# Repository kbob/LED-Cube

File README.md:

# LED Cube

A cube made of RGB LED panels.

I saw [Zaurak's and Polyfloyd's LED cubes](https://kbob.github.io/2019/08/23/led-cubes.html), and decided I wanted to make one too.  This one is smaller with denser LEDs.  (2mm pitch instead of 2.5mm)

# Overview

The cube's faces are six LED panels from Aliexpress.  Each panel has 64&times;64 RGB leds and is driven by the HUB75 protocol.

The chassis is a combination of 3D printed PLA, machine screws, and magnets.
The electronics can be installed and removed without tools.

The electronics consist of a Raspberry Pi connected via USB to an
[iCEBreaker FPGA](https://www.crowdsupply.com/1bitsquared/icebreaker-fpga)
dev board, HUB75 PMOD interface, and the panels.

Power is provided by an eight pack of 18650 batteries and a custom
power supply.  The power board also has an inertial measurement
unit (IMU), battery level monitoring, and soft power controls.

I also have two different display stands that prop the cube up on
one corner.  One stand disassembles for easy transport; the other, shown above,
is more stable and has a (bulky) carrying case.  All this is 3D printed.

# What's Here?

* **Mechanical/** CAD files, STL files, and parts lists.  The two
  display stands are here too.

* **Power Board/** KiCAD files and BOM for the custom power board.

* **Wiring/** Notes on the wiring harness.

* **Linux/** Notes on configuring Linux on the Raspberry Pi.

# What's Missing?

There are several different software options.  I outlined them in
[this 'blog post](https://kbob.github.io/2019-08-23/led-cubes.html).
None of them are in this repository.  I couldn't even begin
to write a comprehensive installation guide for them all.

The gateware is based on [tnt's excellent
ice40-playground](https://github.com/smunaut/ice40-playground).
But I have my own fork [here](https://github.com/kbob/ice40-playground).
My cube uses the `topic-cube` branch.  I haven't checked whether everything
in that branch has made it back upstream.

# What's Coming (I hope)?

## Raspberry Pi 4

My cube has a Raspberry Pi 3 Model A+.  (What a mouthful!)
Shortly after I built it, the Raspberry Pi foundation announced
the Raspberry Pi 4.  Its GPU is much better, and I really want to
get it into my cube.  But of course it's a different size;
I have to redesign part of the chassis to make it fit.

# Mesa OpenGL

I am using Broadcom's proprietary OpenGL.  I want to get the
open source Mesa GL running, but haven't figured out the magic
yet.  (It's complicated because I refuse to install an X11 server;
I only want offscreen rendering.)

# More LED Panels

**Update 2019-09-22:**  Good news!  1BitSquared now has [the correct
LED panels](https://1bitsquared.com/collections/embedded-hardware/products/led-panel)
in stock.  Get the ICN2037 variant.

The Aliexpress vendors do not ship a single version of the HUB75
panels.  Instead, you get whatever vendors happen to be available
surplus.  Each version has different driver chips, timing requirements,
mechanical layout, even power voltage requirements.  So today
the panels on the cube are irreplaceable.  If one dies, I'll
have no cube.

~~Esden is working on getting a reliable source for LED panels.
Follow him on twitter ([@esden](https://twitter.com/esden))
to stay up to date.~~

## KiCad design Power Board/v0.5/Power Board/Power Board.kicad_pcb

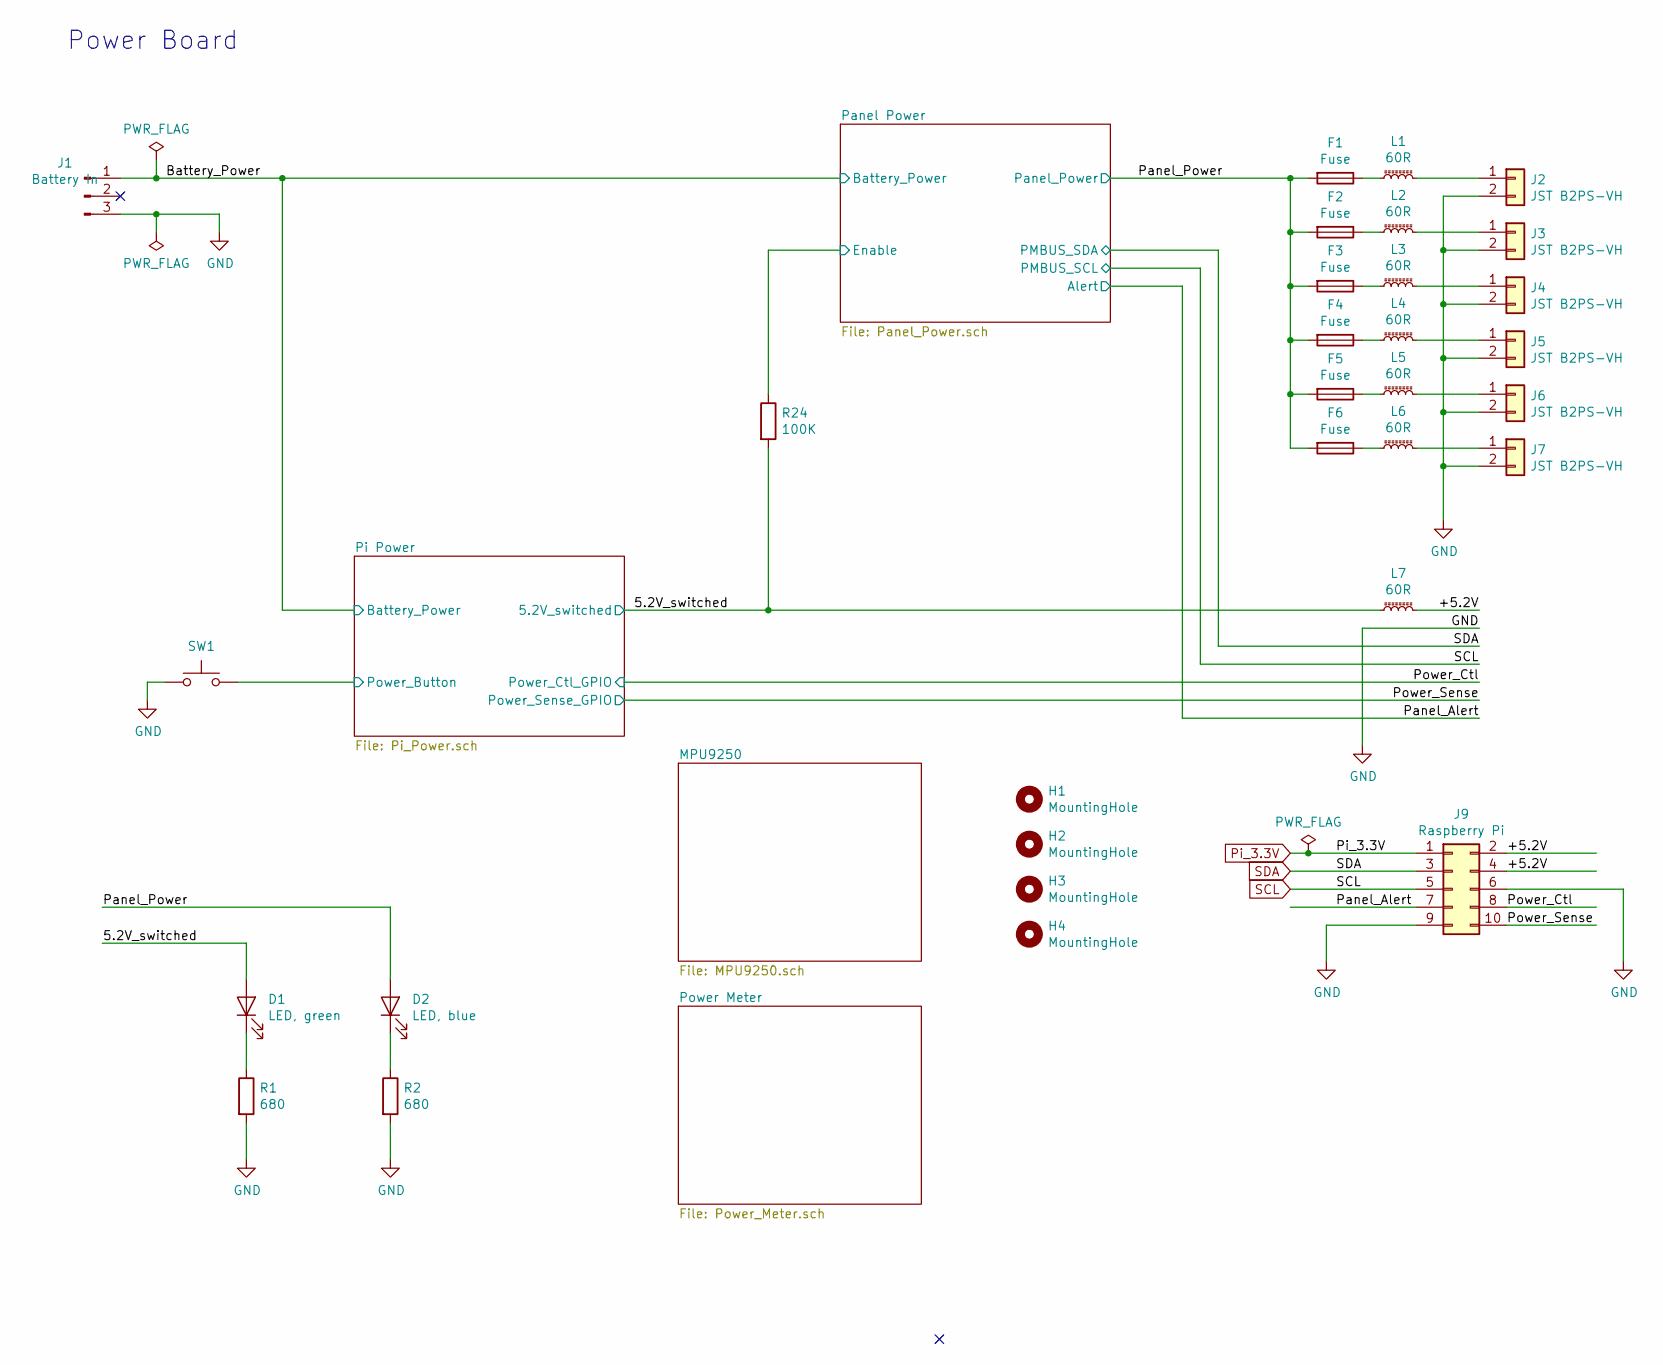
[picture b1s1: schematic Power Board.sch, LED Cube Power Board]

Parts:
D1: LED, green; LED_0603_1608Metric; Part No. LG Q971-KN-1
D2: LED, blue; LED_0603_1608Metric; Part No. LB Q39G-L2N2-35-1
F1, F2, F3, F4, F5, F6: Fuse; Fuse_1206_3216Metric; Part No. NANOSMD400LR-C-2; Digikey No. F9967CT-ND
H1, H2, H3, H4: MountingHole; MountingHole_2.7mm_M2.5
J1: Battery In; JST_VH_B3PS-VH_1x03_P3.96mm_Horizontal; Part No. B3PS-VH(LF)(SN); Digikey No. 455-1649-ND
J2, J3, J4, J5, J6, J7: JST B2PS-VH; JST_VH_B2PS-VH_1x02_P3.96mm_Horizontal; Part No. B2PS-VH(LF)(SN); Digikey No. 455-1648-ND
J9: Raspberry Pi; JST_PUD_S10B-PUDSS-1_2x05_P2.00mm_Horizontal; Part No. S10B-PUDSS-1(LF)(SN); Digikey No. 455-2486-ND
L1, L2, L3, L4, L5, L6, L7: 60R; L_1206_3216Metric; Part No. FBMJ3216HM600-T; Digikey No. 587-1770-1-ND
R1, R2: 680; R_0603_1608Metric_Pad1.05x0.95mm_HandSolder; Part No. RC0603JR-07680R
R24: 100K; R_0603_1608Metric; Part No. RC0603JR-07100K
SW1: SW_Push; PTS645-Vx-39-2; Part No. PTS645VK39-2 LFS; Digikey No. CKN10053-ND

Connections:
/5.2V_switched: D1.2 (A), L7.1, R24.2; also elsewhere on the board
/+5.2V: J9.2, J9.4, L7.2
/Battery_Power: J1.1; also elsewhere on the board
/Panel Power/Enable: R24.1; also elsewhere on the board
/Panel_Alert: J9.7; also elsewhere on the board
/Panel_Power: D2.2 (A), F1.2, F2.2, F3.2, F4.2, F5.2, F6.2; also elsewhere on the board
/Pi Power/Power_Button: SW1.2; also elsewhere on the board
/Power_Ctl: J9.8; also elsewhere on the board
/Power_Sense: J9.10; also elsewhere on the board
GND: J1.3, J2.2, J3.2, J4.2, J5.2, J6.2, J7.2, J9.6, J9.9, R1.2, R2.2, SW1.1; also elsewhere on the board
unnamed: D1.1 (K), R1.1
unnamed: D2.1 (K), R2.1
unnamed: F1.1, L1.1
unnamed: F2.1, L2.1
unnamed: F3.1, L3.1
unnamed: F4.1, L4.1
unnamed: F5.1, L5.1
unnamed: F6.1, L6.1
unnamed: J2.1, L1.2
unnamed: J3.1, L2.2
unnamed: J4.1, L3.2
unnamed: J5.1, L4.2
unnamed: J6.1, L5.2
unnamed: J7.1, L6.2
Pi_3.3V: J9.1; also elsewhere on the board
SCL: J9.5; also elsewhere on the board
SDA: J9.3; also elsewhere on the board

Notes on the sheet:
Power Board

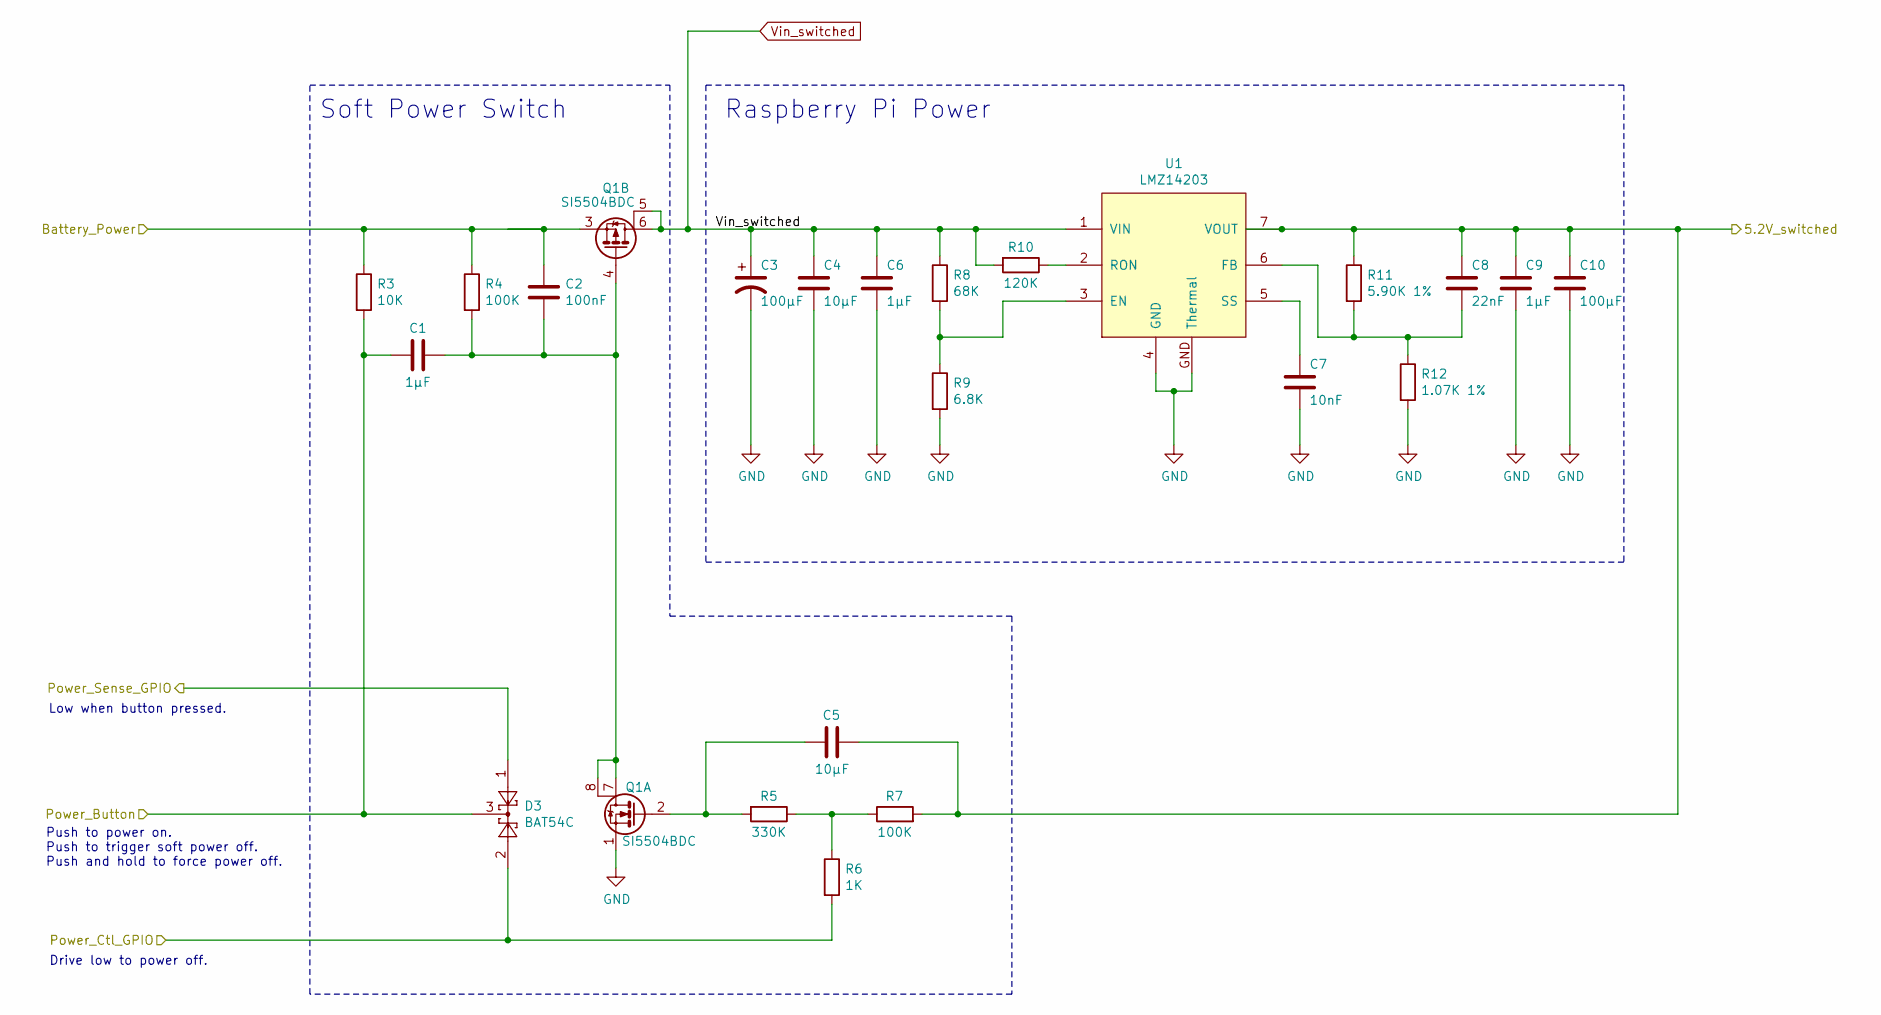
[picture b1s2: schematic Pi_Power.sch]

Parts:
C1, C6, C9: 1µF; C_0805_2012Metric; Part No. GMK212B7105KG-T; Digikey No. 587-1438-1-ND
C2: 100nF; C_0805_2012Metric; Part No. CGA4J2X7R2A104K125AA; Digikey No. 445-5827-1-ND
C3: 100µF; CP_Elec_8x10; Part No. EDK107M050A9MAA; Digikey No. 399-6672-1-ND
C4, C5: 10µF; C_0805_2012Metric; Part No. GRM21BR61E106MA73L; Digikey No. 490-10748-1-ND
C7: 10nF; C_0603_1608Metric; Part No. GRM188R71H103KA01D
C8: 22nF; C_0603_1608Metric; Part No. 885012206091; Digikey No. 732-8009-1-ND
C10: 100µF; C_1210_3225Metric; Part No. LMK325BJ107MM-T; Digikey No. 587-1965-1-ND
D3: BAT54C; SOT-23; Part No. BAT54CTA; Digikey No. BAT54CCT-ND
Q1: SI5504BDC; 1206-8_or_SO-8; Part No. SI5504BDC-T1-GE3; Digikey No. SI5504BDC-T1-GE3CT-ND
R3: 10K; R_0603_1608Metric; Part No. RC0603JR-0710K
R4, R7: 100K; R_0603_1608Metric; Part No. RC0603JR-07100K
R5: 330K; R_0603_1608Metric; Part No. RC0603JR-07330K
R6: 1K; R_0603_1608Metric; Part No. RC0603JR-071K
R8: 68K; R_0603_1608Metric; Part No. RC0603JR-0768K
R9: 6.8K; R_0603_1608Metric; Part No. RC0603JR-076K8
R10: 120K; R_0603_1608Metric; Part No. RC0603JR-07120K
R11: 5.90K 1%; R_0603_1608Metric; Part No. ERJ-3EKF5901V; Digikey No. P5.90KHCT-ND
R12: 1.07K 1%; R_0603_1608Metric; Part No. ERJ-3EKF1071V; Digikey No. P1.07KHCT-ND
U1: LMZ14203; TO-PMOD_7; Part No. LMZ14203TZX-ADJ/NOPB; Digikey No. LMZ14203TZX-ADJ/NOPBCT-ND

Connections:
/5.2V_switched: C5.2, C8.1, C9.1, C10.1, R7.2, R11.1, U1.7 (VOUT); also elsewhere on the board
/Battery_Power: C2.1, Q1.3 (1), R3.1, R4.1; also elsewhere on the board
/Pi Power/Power_Button: C1.2, D3.3, R3.2; also elsewhere on the board
/Power_Ctl: D3.2, R6.2; also elsewhere on the board
/Power_Sense: D3.1; also elsewhere on the board
GND: C3.2, C4.2, C6.2, C7.2, C9.2, C10.2, Q1.1 (S), R9.2, R12.2, U1.4 (GND), U1.GND (Thermal); also elsewhere on the board
unnamed: C1.1, C2.2, Q1.4 (G), Q1.7 (D), Q1.8 (D), R4.2
unnamed: C5.1, Q1.2 (G), R5.2
unnamed: C7.1, U1.5 (SS)
unnamed: C8.2, R11.2, R12.1, U1.6 (FB)
unnamed: R5.1, R6.1, R7.1
unnamed: R8.2, R9.1, U1.3 (EN)
unnamed: R10.1, U1.2 (RON)
Vin_switched: C3.1, C4.1, C6.1, Q1.5 (D), Q1.6 (D), R8.1, R10.2, U1.1 (VIN); also elsewhere on the board

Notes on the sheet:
Raspberry Pi Power
Push to power on. Push to trigger soft power off. Push and hold to force power off.
Drive low to power off.
Soft Power Switch
Low when button pressed.

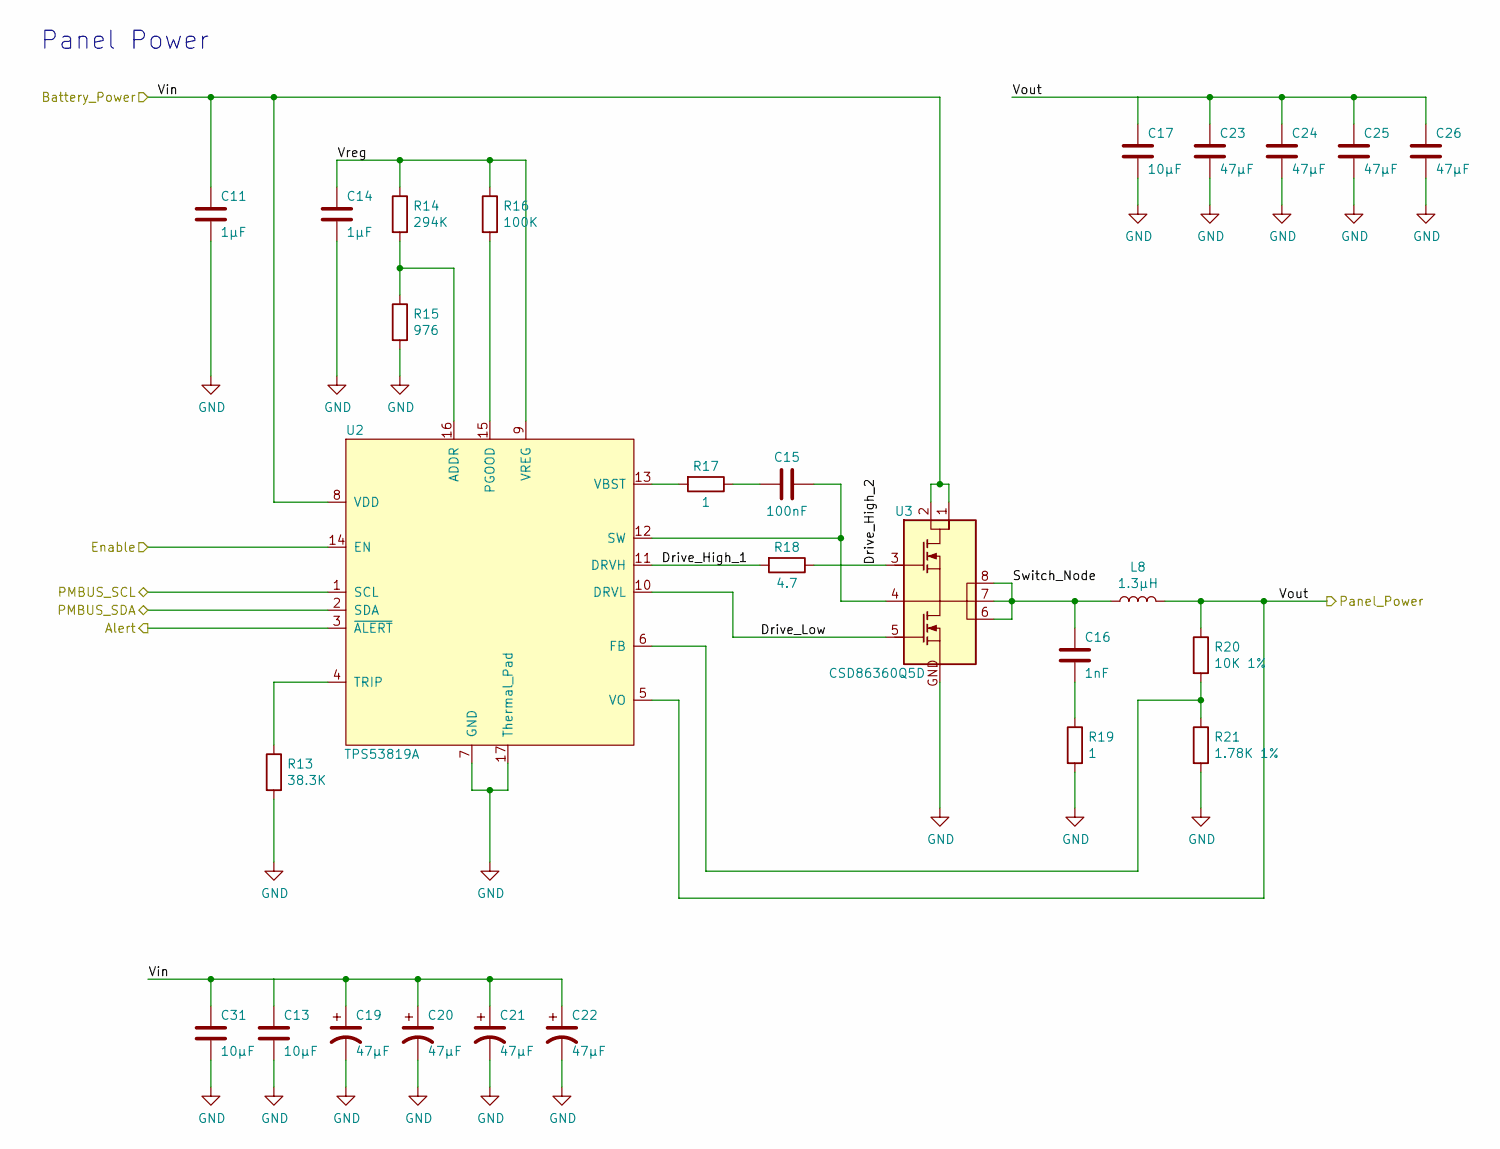
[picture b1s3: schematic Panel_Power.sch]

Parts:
C11, C14: 1µF; C_0805_2012Metric; Part No. GMK212B7105KG-T; Digikey No. 587-1438-1-ND
C13, C17, C31: 10µF; C_1206_3216Metric; Part No. GRM21BR61E106MA73L; Digikey No. 490-10748-1-ND
C15: 100nF; C_0805_2012Metric; Part No. CGA4J2X7R2A104K125AA; Digikey No. 445-5827-1-ND
C16: 1nF; C_0603_1608Metric; Part No. C0603C102J5RACTU; Digikey No. 399-1083-1-ND
C19, C20, C21, C22: 47µF; CP_OSCON_Poly_F12; Part No. 35SVPD47M; Digikey No. PCE5080CT-ND
C23, C24, C25, C26: 47µF; C_1210_3225Metric; Part No. GRM32EC81C476KE15L; Digikey No. 490-10531-1-ND
L8: 1.3µH; Coilcraft_XAL1580; Part No. XAL1580-132MEB; Digikey No. Mouser
R13: 38.3K; R_0603_1608Metric; Part No. RMCF0603FT38K3; Digikey No. RMCF0603FT38K3CT-ND
R14: 294K; R_0402_1005Metric; Part No. CRCW0402294KFKED; Digikey No. 541-294KLCT-ND
R15: 976; R_0402_1005Metric; Part No. CRCW0402976RFKED; Digikey No. 541-976LCT-ND
R16: 100K; R_0603_1608Metric; Part No. RC0603JR-07100K
R17, R19: 1; R_0805_2012Metric; Part No. CRCW08051R00FKEA; Digikey No. 541-1.00CCCT-ND
R18: 4.7; R_0805_2012Metric; Part No. ERJ-6RQF4R7V; Digikey No. P4.7DCT-ND
R20: 10K 1%; R_0603_1608Metric; Part No. RNCP0603FTD10K0; Digikey No. RNCP0603FTD10K0CT-ND
R21: 1.78K 1%; R_0603_1608Metric; Part No. RC0603FR-0717K8L; Digikey No. 311-17.8KHRCT-ND
U2: TPS53819A; VQFN-16-1EP_3x3mm_P0.5mm_EP1.68x1.68mm_ThermalVias; Part No. TPS53819ARGTR; Digikey No. 296-35480-1-ND
U3: CSD86360Q5D; Q5D; Part No. CSD86360Q5D; Digikey No. 296-35026-1-ND

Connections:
/Battery_Power: C11.1, C13.1, C19.1, C20.1, C21.1, C22.1, C31.1, U2.8 (VDD), U3.1 (VIN), U3.2 (VIN); also elsewhere on the board
/Panel Power/Drive_High_1: R18.2, U2.11 (DRVH)
/Panel Power/Drive_High_2: R18.1, U3.3 (TG)
/Panel Power/Drive_Low: U2.10 (DRVL), U3.5 (BG)
/Panel Power/Enable: U2.14 (EN); also elsewhere on the board
/Panel Power/Switch_Node: C16.1, L8.1, U3.6 (VSW), U3.7 (VSW), U3.8 (VSW)
/Panel Power/Vreg: C14.1, R14.1, R16.1, U2.9 (VREG)
/Panel_Alert: U2.3 (~ALERT); also elsewhere on the board
/Panel_Power: C17.1, C23.1, C24.1, C25.1, C26.1, L8.2, R20.1, U2.5 (VO); also elsewhere on the board
GND: C11.2, C13.2, C14.2, C17.2, C19.2, C20.2, C21.2, C22.2, C23.2, C24.2, C25.2, C26.2, C31.2, R13.2, R15.2, R19.2, R21.2, U2.7 (GND), U2.17 (Thermal_Pad), U3.GND; also elsewhere on the board
unnamed: C15.1, U2.12 (SW), U3.4 (TGR)
unnamed: C15.2, R17.1
unnamed: C16.2, R19.1
unnamed: R13.1, U2.4 (TRIP)
unnamed: R14.2, R15.1, U2.16 (ADDR)
unnamed: R16.2, U2.15 (PGOOD)
unnamed: R17.2, U2.13 (VBST)
unnamed: R20.2, R21.1, U2.6 (FB)
SCL: U2.1 (SCL); also elsewhere on the board
SDA: U2.2 (SDA); also elsewhere on the board

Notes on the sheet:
Panel Power

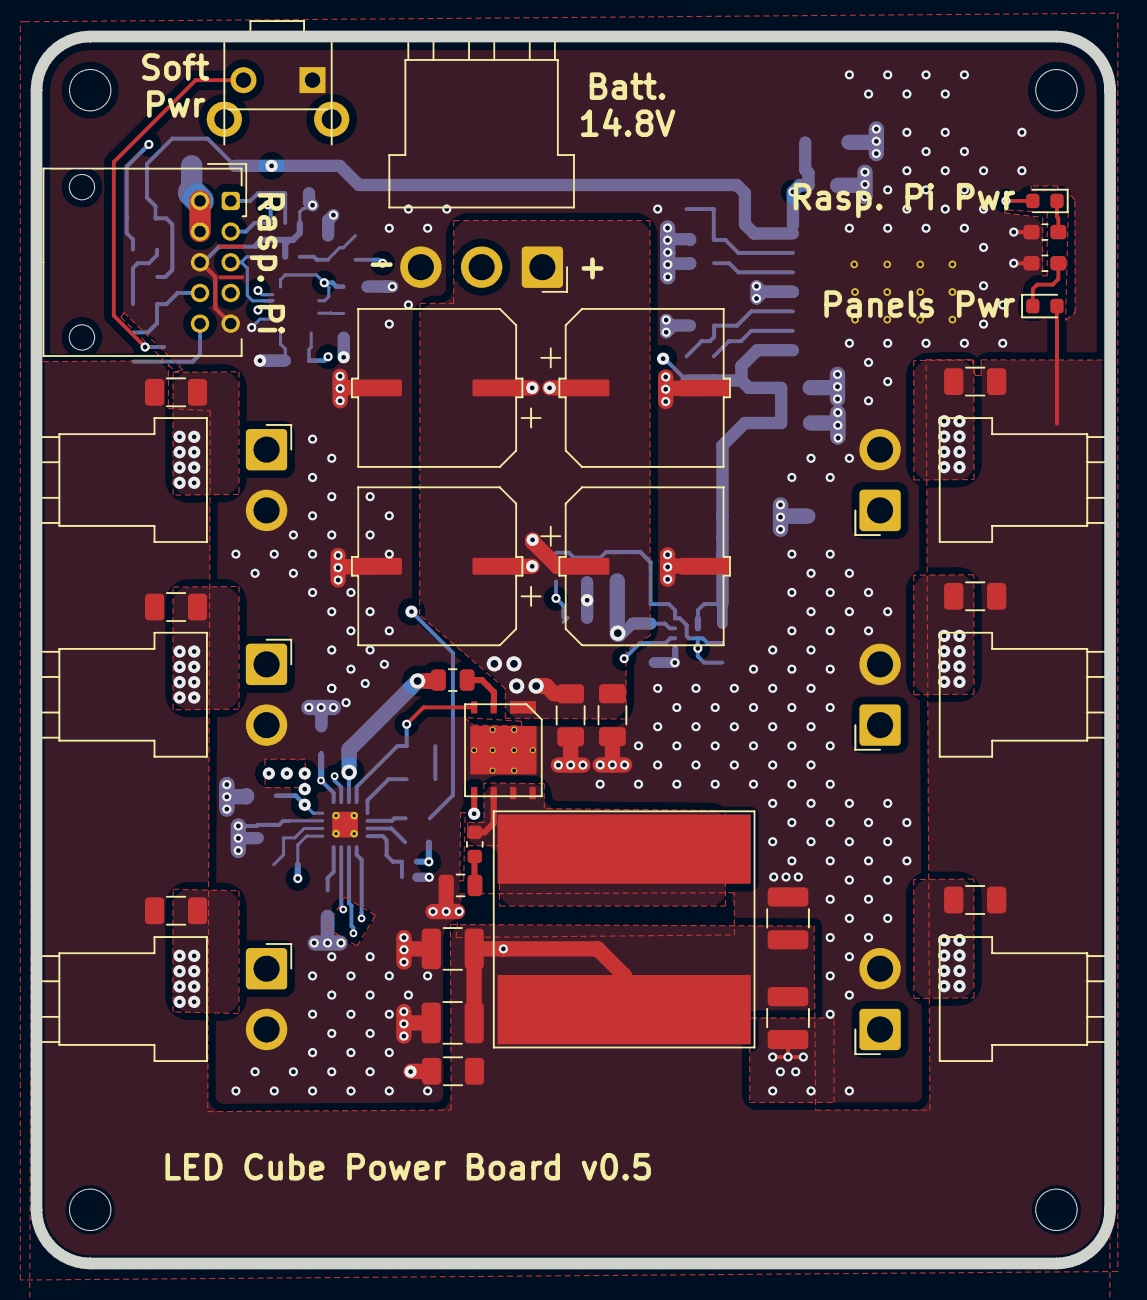
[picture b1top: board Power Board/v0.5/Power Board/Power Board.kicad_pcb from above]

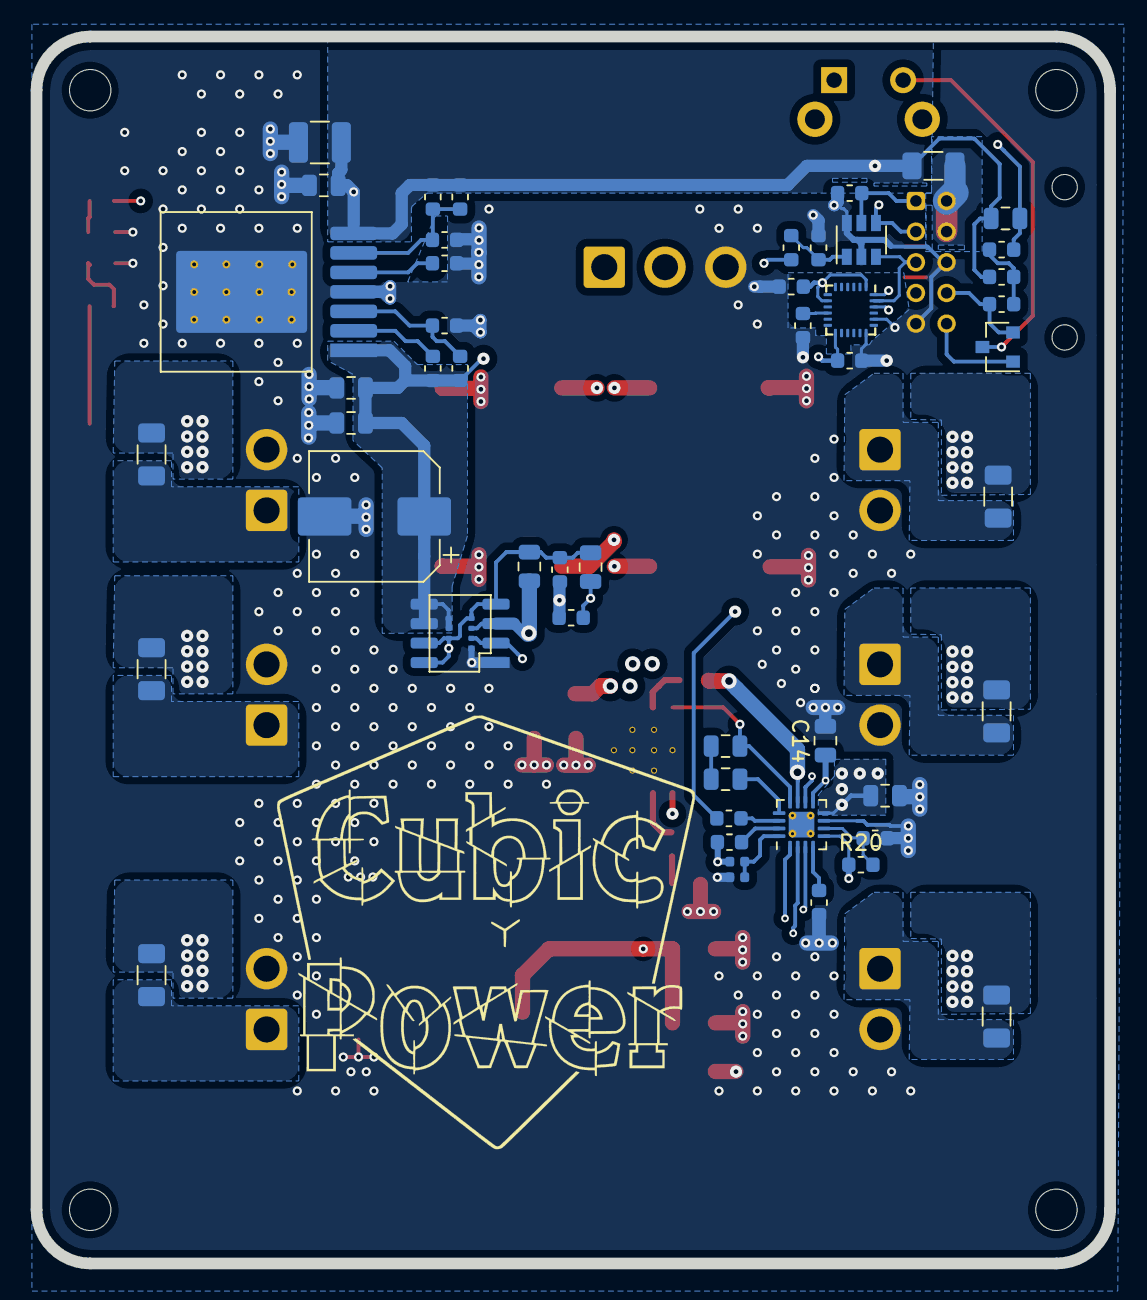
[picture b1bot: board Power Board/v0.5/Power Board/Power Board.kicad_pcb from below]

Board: 4 copper layers, 70.0 x 80.0 mm, 89 parts (50 on the bottom side), 50 nets.

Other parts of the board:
C27, C28, C30: 100nF; C_0603_1608Metric
C29: 10nF; C_0603_1608Metric
R22: 10K 1%; R_0603_1608Metric
R23: 1.78K 1%; R_0603_1608Metric
U4: MPU-9250; InvenSense_QFN-24_3x3mm_P0.4mm
U5: ADS1000; SOT-23-6

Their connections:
GND: C27.2, C28.2, C29.2, C30.2, R23.2, U4.18, U4.20, U5.2, U5.6; also elsewhere on the board
unnamed: C28.1, U4.10
unnamed: R22.2, R23.1, U5.1
Pi_3.3V: C27.1, C29.1, C30.1, U4.1, U4.8, U4.13, U4.22, U5.5; also elsewhere on the board
SCL: U4.23, U5.3; also elsewhere on the board
SDA: U4.24, U5.4; also elsewhere on the board
Vin_switched: R22.1; also elsewhere on the board

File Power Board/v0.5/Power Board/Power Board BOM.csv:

Reference, Quantity, Value, Footprint, Datasheet, Digikey No., Manufacturer, Part No., Package
C10 ,1,"100µF","Capacitor_SMD:C_1210_3225Metric","~","587-1965-1-ND","Taiyo Yuden","LMK325BJ107MM-T",""
C16 ,1,"1nF","Capacitor_SMD:C_0603_1608Metric","~","399-1083-1-ND","Kemet","C0603C102J5RACTU",""
C17 C13 C31 ,3,"10µF","Capacitor_SMD:C_1206_3216Metric","~","490-10748-1-ND","Murata","GRM21BR61E106MA73L",""
C19 C20 C21 C22 ,4,"47µF","Power_Board:CP_OSCON_Poly_F12","~","PCE5080CT-ND","Panasonic","35SVPD47M",""
C2 C15 ,2,"100nF","Capacitor_SMD:C_0805_2012Metric","~","445-5827-1-ND","TDK","CGA4J2X7R2A104K125AA",""
C23 C24 C25 C26 ,4,"47µF","Capacitor_SMD:C_1210_3225Metric","~","490-10531-1-ND","Murata","GRM32EC81C476KE15L",""
C28 C27 C30 ,3,"100nF","Capacitor_SMD:C_0603_1608Metric","~","-","Murata","GRM188R71C104KA01D",""
C3 ,1,"100µF","Capacitor_SMD:CP_Elec_8x10","https://datasheet.octopart.com/EDK107M050A9MAA-Kemet-datashe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","399-6672-1-ND","Kemet","EDK107M050A9MAA",""
C5 C4 ,2,"10µF","Capacitor_SMD:C_0805_2012Metric","~","490-10748-1-ND","Murata","GRM21BR61E106MA73L",""
C6 C9 C1 C14 C11 ,5,"1µF","Capacitor_SMD:C_0805_2012Metric","~","587-1438-1-ND","Taiyo Yuden","GMK212B7105KG-T",""
C7 C29 ,2,"10nF","Capacitor_SMD:C_0603_1608Metric","~","-","Murata","GRM188R71H103KA01D","0603"
C8 ,1,"22nF","Capacitor_SMD:C_0603_1608Metric","~","732-8009-1-ND","Wurth","885012206091",""
D1 ,1,"LED, green","LED_SMD:LED_0603_1608Metric","~","-","Osram","LG Q971-KN-1",""
D2 ,1,"LED, blue","LED_SMD:LED_0603_1608Metric","~","-","Osram","LB Q39G-L2N2-35-1",""
D3 ,1,"BAT54C","Package_TO_SOT_SMD:SOT-23","https://www.diodes.com/_files/datasheets/ds11005.pdf","BAT54CCT-ND","Diodes Inc.","BAT54CTA",""
F6 F5 F4 F3 F2 F1 ,6,"Fuse","Power_Board:Fuse_1206_3216Metric","~","F9967CT-ND","Littelfuse","NANOSMD400LR-C-2",""
H1 H2 H3 H4 ,4,"MountingHole","MountingHole:MountingHole_2.7mm_M2.5","~","-","-","-",""
J1 ,1,"Battery In","Power_Board:JST_VH_B3PS-VH_1x03_P3.96mm_Horizontal","","455-1649-ND","JST","B3PS-VH(LF)(SN)",""
J7 J6 J5 J4 J3 J2 ,6,"JST B2PS-VH","Power_Board:JST_VH_B2PS-VH_1x02_P3.96mm_Horizontal","~","455-1648-ND","JST","B2PS-VH(LF)(SN)",""
J9 ,1,"Raspberry Pi","Connector_JST:JST_PUD_S10B-PUDSS-1_2x05_P2.00mm_Horizontal","~","455-2486-ND","JST","S10B-PUDSS-1(LF)(SN)",""
L1 L2 L3 L4 L5 L6 L7 ,7,"60R","Inductor_SMD:L_1206_3216Metric","https://ds.yuden.co.jp/TYCOMPAS/ut/detail?pn=FBMJ3216HM600-T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","587-1770-1-ND","Taiyo Yuden","FBMJ3216HM600-T",""
L8 ,1,"1.3µH","Power_Board:Coilcraft_XAL1580","~","Mouser","Coilcraft","XAL1580-132MEB",""
Q1 ,1,"SI5504BDC","Power_Board:1206-8_or_SO-8","http://www.vishay.com/docs/74483/si5504bdc.pdf","SI5504BDC-T1-GE3CT-ND","Vishay","SI5504BDC-T1-GE3",""
R10 ,1,"120K","Resistor_SMD:R_0603_1608Metric","~","-","Yageo","RC0603JR-07120K","0603"
R11 ,1,"5.90K 1%","Resistor_SMD:R_0603_1608Metric","~","P5.90KHCT-ND","Panasonic","ERJ-3EKF5901V","0603"
R12 ,1,"1.07K 1%","Resistor_SMD:R_0603_1608Metric","~","P1.07KHCT-ND","Panasonic","ERJ-3EKF1071V","0603"
R13 ,1,"38.3K","Resistor_SMD:R_0603_1608Metric","~","RMCF0603FT38K3CT-ND","Stackpole","RMCF0603FT38K3",""
R14 ,1,"294K","Resistor_SMD:R_0402_1005Metric","~","541-294KLCT-ND","Vishay-Dale","CRCW0402294KFKED",""
R15 ,1,"976","Resistor_SMD:R_0402_1005Metric","~","541-976LCT-ND","VIshay-Dale","CRCW0402976RFKED",""
R17 R19 ,2,"1","Resistor_SMD:R_0805_2012Metric","~","541-1.00CCCT-ND","Vishay-Dale","CRCW08051R00FKEA",""
R18 ,1,"4.7","Resistor_SMD:R_0805_2012Metric","~","P4.7DCT-ND","Panasonic","ERJ-6RQF4R7V",""
R2 R1 ,2,"680","Resistor_SMD:R_0603_1608Metric_Pad1.05x0.95mm_HandSolder","~","-","Yageo","RC0603JR-07680R",""
R20 R22 ,2,"10K 1%","Resistor_SMD:R_0603_1608Metric","~","RNCP0603FTD10K0CT-ND","Stackpole","RNCP0603FTD10K0",""
R21 R23 ,2,"1.78K 1%","Resistor_SMD:R_0603_1608Metric","~","311-17.8KHRCT-ND","Yageo","RC0603FR-0717K8L",""
R24 R7 R4 R16 ,4,"100K","Resistor_SMD:R_0603_1608Metric","~","-","Yageo","RC0603JR-07100K",""
R3 ,1,"10K","Resistor_SMD:R_0603_1608Metric","~","-","Yageo","RC0603JR-0710K",""
R5 ,1,"330K","Resistor_SMD:R_0603_1608Metric","~","-","Yageo","RC0603JR-07330K",""
R6 ,1,"1K","Resistor_SMD:R_0603_1608Metric","~","-","Yageo","RC0603JR-071K",""
R8 ,1,"68K","Resistor_SMD:R_0603_1608Metric","~","-","Yageo","RC0603JR-0768K","0603"
R9 ,1,"6.8K","Resistor_SMD:R_0603_1608Metric","~","-","Yageo","RC0603JR-076K8","0603"
SW1 ,1,"SW_Push","Power_Board:PTS645-Vx-39-2","~","CKN10053-ND","C&K","PTS645VK39-2 LFS",""
U1 ,1,"LMZ14203","Power_Board:TO-PMOD_7","","LMZ14203TZX-ADJ/NOPBCT-ND","TI"," LMZ14203TZX-ADJ/NOPB ","TO-PMOD 7"
U2 ,1,"TPS53819A","Power_Board:VQFN-16-1EP_3x3mm_P0.5mm_EP1.68x1.68mm_ThermalVias","","296-35480-1-ND","TI","TPS53819ARGTR",""
U3 ,1,"CSD86360Q5D","Power_Board:Q5D","","296-35026-1-ND","TI","CSD86360Q5D",""
U4 ,1,"MPU-9250","Sensor_Motion:InvenSense_QFN-24_3x3mm_P0.4mm","https://store.invensense.com/datasheets/invensense/MPU9250RE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","1428-1019-1-ND","InvenSense","MPU-9250",""
U5 ,1,"ADS1000","Package_TO_SOT_SMD:SOT-23-6","http://www.ti.com/lit/ds/symlink/ads1000.pdf","296-38847-1-ND","TI","ADS1000A0IDBVR",""

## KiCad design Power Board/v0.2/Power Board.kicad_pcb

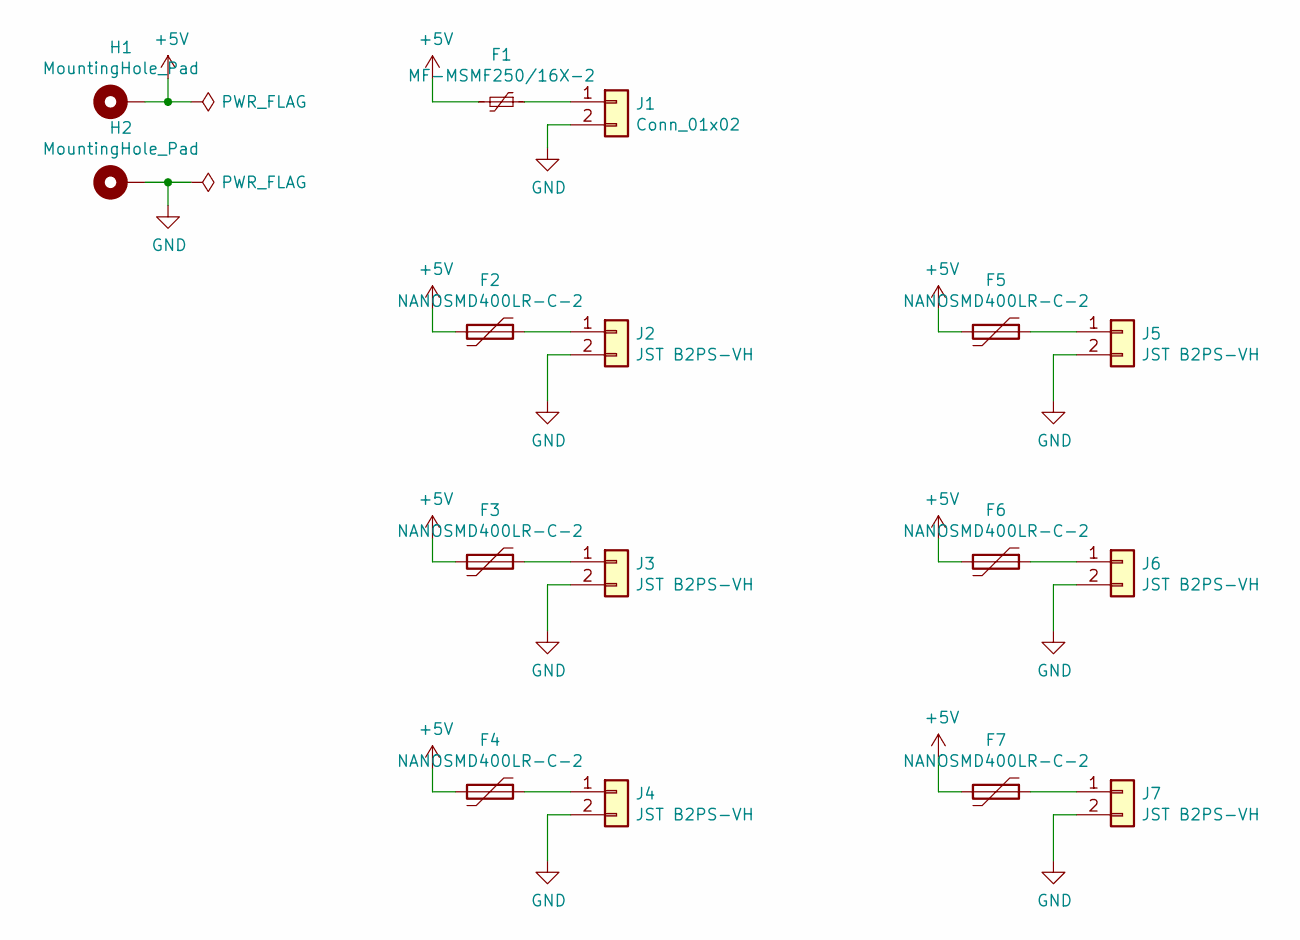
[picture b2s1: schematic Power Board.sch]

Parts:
F1: MF-MSMF250/16X-2; Bourns MF-MSMF Style 2
F2, F3, F4, F5, F6, F7: NANOSMD400LR-C-2; Fuse_1206_3216Metric
H1, H2: MountingHole_Pad; MountingHole_3mm_Pad
J1: Conn_01x02; PinSocket_1x02_P2.54mm_Horizontal
J2, J3, J4, J5, J6, J7: JST B2PS-VH; JST_VH_B2PS-VH_1x02_P3.96mm_Horizontal

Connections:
+5V: F1.2, F2.2, F3.2, F4.2, F5.2, F6.2, F7.2, H1.1
GND: H2.1, J1.2, J2.2, J3.2, J4.2, J5.2, J6.2, J7.2
unnamed: F1.1, J1.1
unnamed: F2.1, J2.1
unnamed: F3.1, J3.1
unnamed: F4.1, J4.1
unnamed: F5.1, J5.1
unnamed: F6.1, J6.1
unnamed: F7.1, J7.1

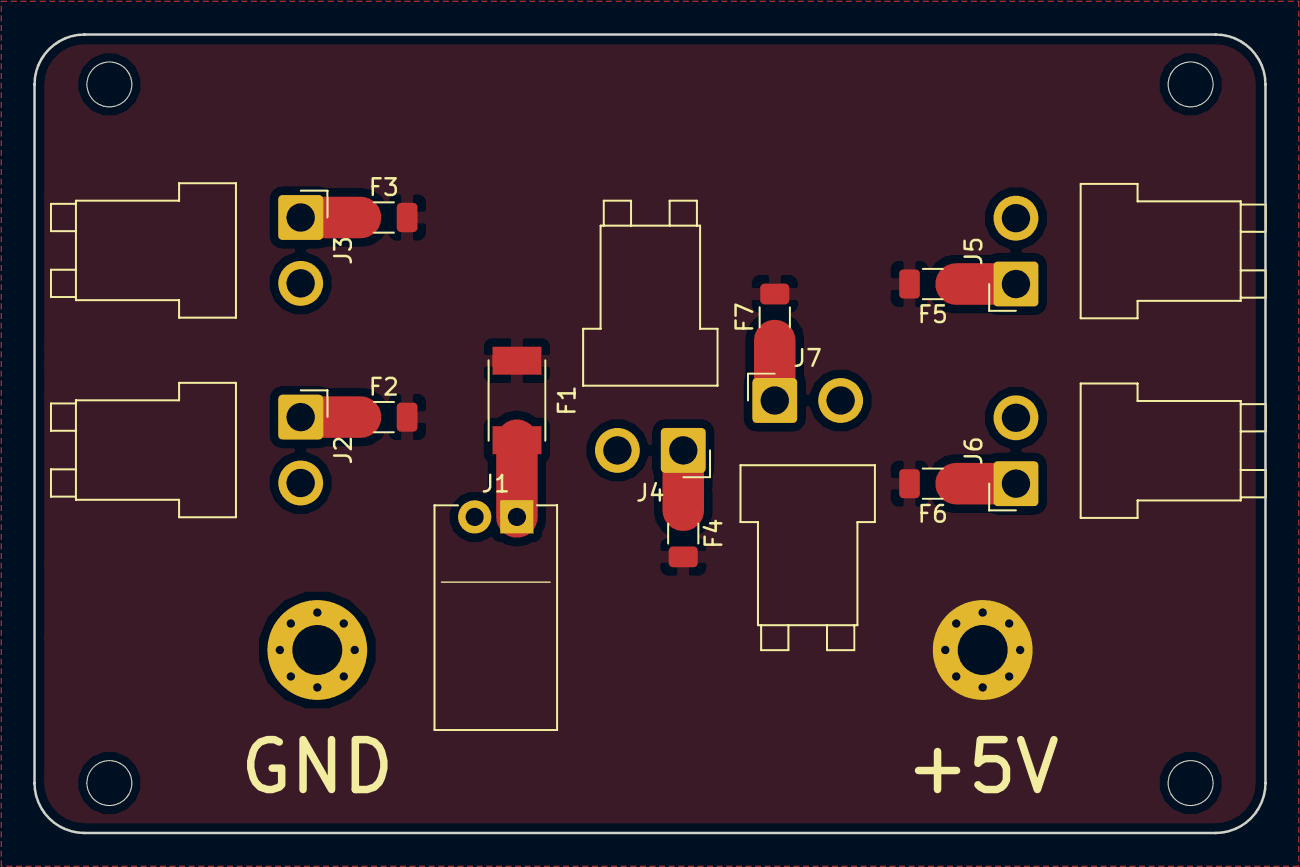
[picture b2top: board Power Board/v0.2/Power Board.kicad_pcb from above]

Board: 2 copper layers, 74.0 x 48.0 mm, 16 parts (0 on the bottom side), 9 nets.

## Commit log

2019-02-17 Power distribution board v0.1
2019-03-17 power board v0.2. Smaller fuses, smaller board.
2019-03-17 Add a README.
2019-03-20 Work in progress on v0.3 of power board.
2019-03-22 power board v0.3 - Raspberry Pi side only
2019-03-26 Oops, a no-connect was misaligned.
2019-03-26 Revised soft power switch. Now switches power to 5V regulator.
2019-03-27 Add datasheets.
2019-03-27 Remove Pi_Power.sch
2019-03-27 Rename Soft_Switch.sch to Pi_Power.sch
2019-03-28 Create the LED panel supply circuit.
2019-04-02 Update components with available parts.
2019-04-02 Document Raspberry Pi P1 connector wiring.
2019-04-03 Draw all custom footprints and assign to components.
2019-04-04 Work in progress.
2019-04-06 L8 footprint is Coilcraft XAL1580, not some Kemet cap.
2019-04-07 Start Power Board v0.4 by copying v0.3.
2019-04-07 Update schematic with panel power Cin, Cout.
2019-04-07 Update panel power with Cin, Cout.
2019-04-09 Add or correct courtyards.
2019-04-09 New 4 Layer Layout
    Needed 4 layers and double sided design in order to make everything fit
2019-04-11 Preliminary Layout Started
    Have most of the components moved to reasonable locations.
    Initial layout placeholders to get a general sense of connections.
    Added a sheet with the MPU-9250 Circuit but not pushed to board yet.
    Still need to add a lot of copper pours and stitching.
2019-04-12 More Layout Work
    Just another preliminary update so we can both work on changes
2019-04-14 Updated board dimensions and mt. holes, tweaked MPU schematic.
2019-04-14 Change keep-out text.
2019-04-15 Widen board to 70mm, delineate mechanical keepout zones.
2019-04-15 Revert "Change keep-out text."
    This reverts commit ca402f97387596ad30b5b3e9a838d0bd200cb8e0.
2019-04-15 Revert "Updated board dimensions and mt. holes, tweaked MPU schematic."
    This reverts commit 6936a160ef8a0f8efd2e8f2d18775030a6ae8800.
2019-04-16 Add ADC to monitor battery voltage.
2019-04-18 Almost Rough Draft Done
    Mostly routed but needs lots of TLC. Need to check rule definitions before DRC
2019-04-19 More routing and zone placements. Needs more TLC Needs DRC review and fix
2019-04-20 Better ground flow through Q1 Need to add more copper for panel connector between fuse and ferrite
2019-04-20 Changed connections to panel connectors. Did some of the TLC work on the pours. Still need to fix DRC, mostly for U2 clearance issues that aren't really a DRC
2019-04-21 Tracks and rules tweaked to eliminate most DRC 2 DRC errors remain which don't seem valid
2019-04-22 Final Cleanup 2 DRC Errors that seem false Silkscreen needs work
2019-04-23 Rework routing to panel connectors. WIP.
2019-04-23 Reattach LED to Panel_Power.
2019-04-24 George broke the ground pour. Why?
2019-04-25 Modified zones on the left side of the board
2019-04-26 Notes on Raspberry Pi Linux configuration
2019-04-26 More Zones Changes/Improvements
2019-04-27 Final Layout
    Just need silk screen cleanup
2019-04-27 Add to Linux/README.
2019-04-28 Add 3D models for some components.
2019-04-28 Add 3D models for more components.
2019-04-28 Clean up silkscreen, add logo artwork.
2019-04-28 Add GIMP file for logo artwork.
2019-04-30 Linux config: add avahi ssh service.
2019-04-30 Change In1.Cu ground pour to use solid connections to through holes.
2019-04-30 Update BOM. Change R20 to 0603 package.
2019-05-02 Add BOM massage script. Add generated files: schematic PDF, BOM CSVs, Gerbers, drill file.
2019-05-26 Start a record of installed packages.
2019-05-28 Create power board v0.5.
2019-05-28 Update version number on silkscreen.
2019-05-28 Set solder mask minimum width to zero.
2019-06-01 Document the wiring.
2019-06-01 Document Pi-to-Power wire length.
2019-06-08 Escape bare hyphens in tables?
2019-06-08 Try no hyphen at all.
2019-06-08 Remove leading spaces so tables format.
2019-06-11 Correct Coilcraft XAL1580 footprint: enlarge pads, break up paste areas.
2019-06-11 Correct C14 footprint, remove C6 and C9 incorrect package.
2019-06-11 Create generated files: Schematic, BOM, Digikey, iBOM, Gerber, Excellon.
2019-06-16 Update list of Raspbian packages installed.
2019-07-06 Update Linux install history.
2019-07-06 Correct path to Avahi service file in Linux/README.md.
2019-09-01 update README, include Fusion 360 files.
2019-09-01 add STL files.
2019-09-02 Add lots of mechanical design files and pictures.
2019-09-02 try to fix cube photo orientation.
2019-09-22 LED panels are now available from 1BitSquared.
2019-09-28 fix typo in markdown hyperlink.
